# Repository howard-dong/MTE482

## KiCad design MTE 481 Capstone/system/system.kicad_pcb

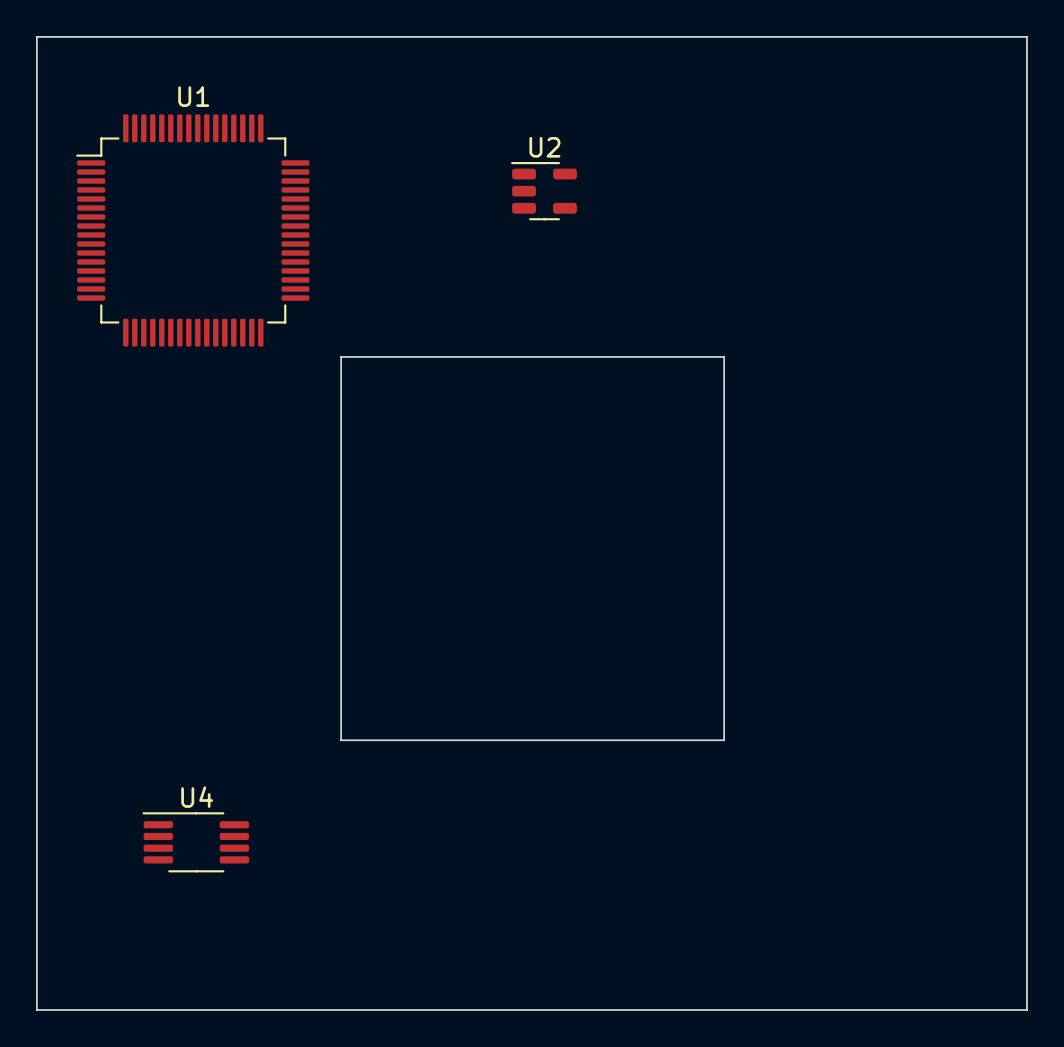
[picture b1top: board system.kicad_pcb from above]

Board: 2 copper layers, 55.0 x 54.1 mm, 3 parts (0 on the bottom side), 6 nets, no tracks yet.

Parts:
U1: STM32F401RETx; LQFP-64_10x10mm_P0.5mm
U2: MCP6001-OT; SOT-23-5
U4: MCP9808_MSOP; MSOP-8_3x3mm_P0.65mm

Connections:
/GSR Lead +: U1.1 (VBAT), U1.13 (VREF+), U1.19 (VDD), U1.32 (VDD), U1.48 (VDD), U1.64 (VDD), U4.8 (V_{DD})
GND: U1.18 (VSS), U1.31 (VSS), U1.47 (VSS), U1.60 (BOOT0), U1.63 (VSS), U2.2 (V-), U4.4 (GND)
unnamed: U2.3 (+), U2.5 (V+)
unnamed: U1.15 (PA1), U2.1
unnamed: U1.55 (PB3), U4.1 (SDA)
unnamed: U1.29 (PB10), U4.2 (SCL)

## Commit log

2024-01-29 Electrical stuff
2024-01-29 part models
2024-03-07 Iniital commit for main
2024-03-07 first pass merging arduino into stm
2024-03-13 stm32->arduino. ex of pwm on non-timer pin?
2024-03-18 syncing stuff
2024-03-22 format changes
2024-03-25 i2c support files; main updated in next commit
2024-03-25 obtain bpm
